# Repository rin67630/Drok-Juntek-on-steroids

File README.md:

# Drok&Juntek on steroids.
Extend the possibilities of cheap digital power supplies with an ESP32 WiFi module

N.B.   The Software part is now on  
https://github.com/rin67630/Soft-Power2-MPPT  
cu there...

Juntek (aka MingHe) and Drok (maybe others e.g Ming-He) sell some interesting cheap programmable buck converter modules e.g.:
- DPS3806         (60V/6A boost/buck converter) https://www.aliexpress.com/item/1005001591485527.html
- Buck3603        (36V/3A buck converter) https://www.aliexpress.com/item/32872687512.html
- BST900          (36V/90V boost converter https://www.aliexpress.com/item/1005002006504263.html
- Drok low Power  (60V/8A buck converter) https://www.aliexpress.com/item/32862110549.html  
- Drok high power (80V/12A buck converter) https://www.aliexpress.com/item/32863179021.html  
*(links only given to identify the modules, you are encouraged to procure the devices from your favourite source)  

They are all controlled by a pluggable control board, which stages a STM microcontroller and a 4x7 digit LED display.  
The 4 push-buttons to control the operations are clumsy and the seven segment display is everything but comfortable.  

My idea was to get rid of the original control module, and to replace it by an ESP32 WiFi enabled microcontroller in order to boost it's usability,
give full internet control and provide tons of features... 

Drok and Juntek are using the same analog control principle:  on the left side, the connector gets two PWM control inputs (voltage and current) and deliver two corresponding analog control feedback outputs all in the range 0..2,1V.  
On the right side, the connector provides GND and 5V at ~200mA.  

I used a TTGO ESP32 with an integrated TFT color display plugged onto a 6x8cm prototyping board as an adapter on a Drok 6008  
showing the web interface on a smartphone:   
  
Here the version with a PCB on a Drok6012 with input and load current probes and a rotary encoder on the extension port:   

The BOM for the upgrade cost less than 20$ (the ESP TTGO, an ADS1115 module, a prototyping board, some pin headers, a few resistors and condensators...)  

## The fun can begin!
Recycling a big part of the software resources of https://github.com/rin67630/Soft-Power-MPPT, I am providing much more than just a simple programmable power supply.

### Power supply mode
The power supply is controllable by:   
- USB -Serial with a simple menu to change the set-points control, the OLED display variants, the charging profiles and print reports.  
- from everywhere in the world using the cloud dashboard service of https://thinger.io with a free limited maker account.  
This is just an example, much more will come:  

- using the integrated buttons of the TTGO and/or an optional rotary knob to make it more comfortable to control.  
- can optionally be remotely controlled by another "slave" TTGO module in the same WiFi area.

Over the serial port and thinger.io, many reports will be made available:  
- Energy report by the second, the minute, the hour.
- Ah, Wh Joule/Coulomb reports by the minutes, the hour, the day.
- Events of the charging process
- ...  

Beside the usual constant voltage and constant current set points, I will provide many interesting things that are not common, but very useful:

### MPPT Solar charger:
cf: https://github.com/rin67630/Soft-Power2-MPPT

### Battery Charger mode: (1)  
- charging profiles for many battery chemistries
- evaluation of the battery's internal resistance
- evaluation of the battery' capacity
- charging time series plots

### Power Source emulation: (1)  
- add a programmable internal resistance
- run a constant power mode
- emulation of solar panel / wind turbine incuding "pseudo-daily" gaussian cycles (accelerated 60x) to test solar chargers

### Programmable Load (for the Juntek buck-boost version) (1)  
- together with a flooder to dissipate the energy, the buck-boost converter can be used to discharge batteries and transfer energy from one battery to another one.  

### Maybe other useful ideas that you might have...

Last but not least everything is neatly self powered, and integrated on one single board, that plugs instead of the original controller board.  
If you wanted to revert to the original functionality, just replug the manufacturer's control board.  
There is absolutely no cable mess and even a new program can be updated over the air using a beginner's easy Arduino IDE.  
You need no additional computer to manage the dashboards, everything is done in the cloud.  
The only thing you need, is a Wifi connection.  

(1) not yet finalized...

You are invited to discuss your personal project on Discord:  
https://discord.gg/gcmSpHH3bX  (Multi purpose Hardware)  
https://discord.gg/eY5H6PMqfk  (Specific application as a MPPT Solar Charge Controller).  

Cu there!

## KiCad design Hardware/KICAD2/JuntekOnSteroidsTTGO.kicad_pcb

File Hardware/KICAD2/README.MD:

New optimized PCB layout Courtesy paulvdh@forum.KiCAD.info.

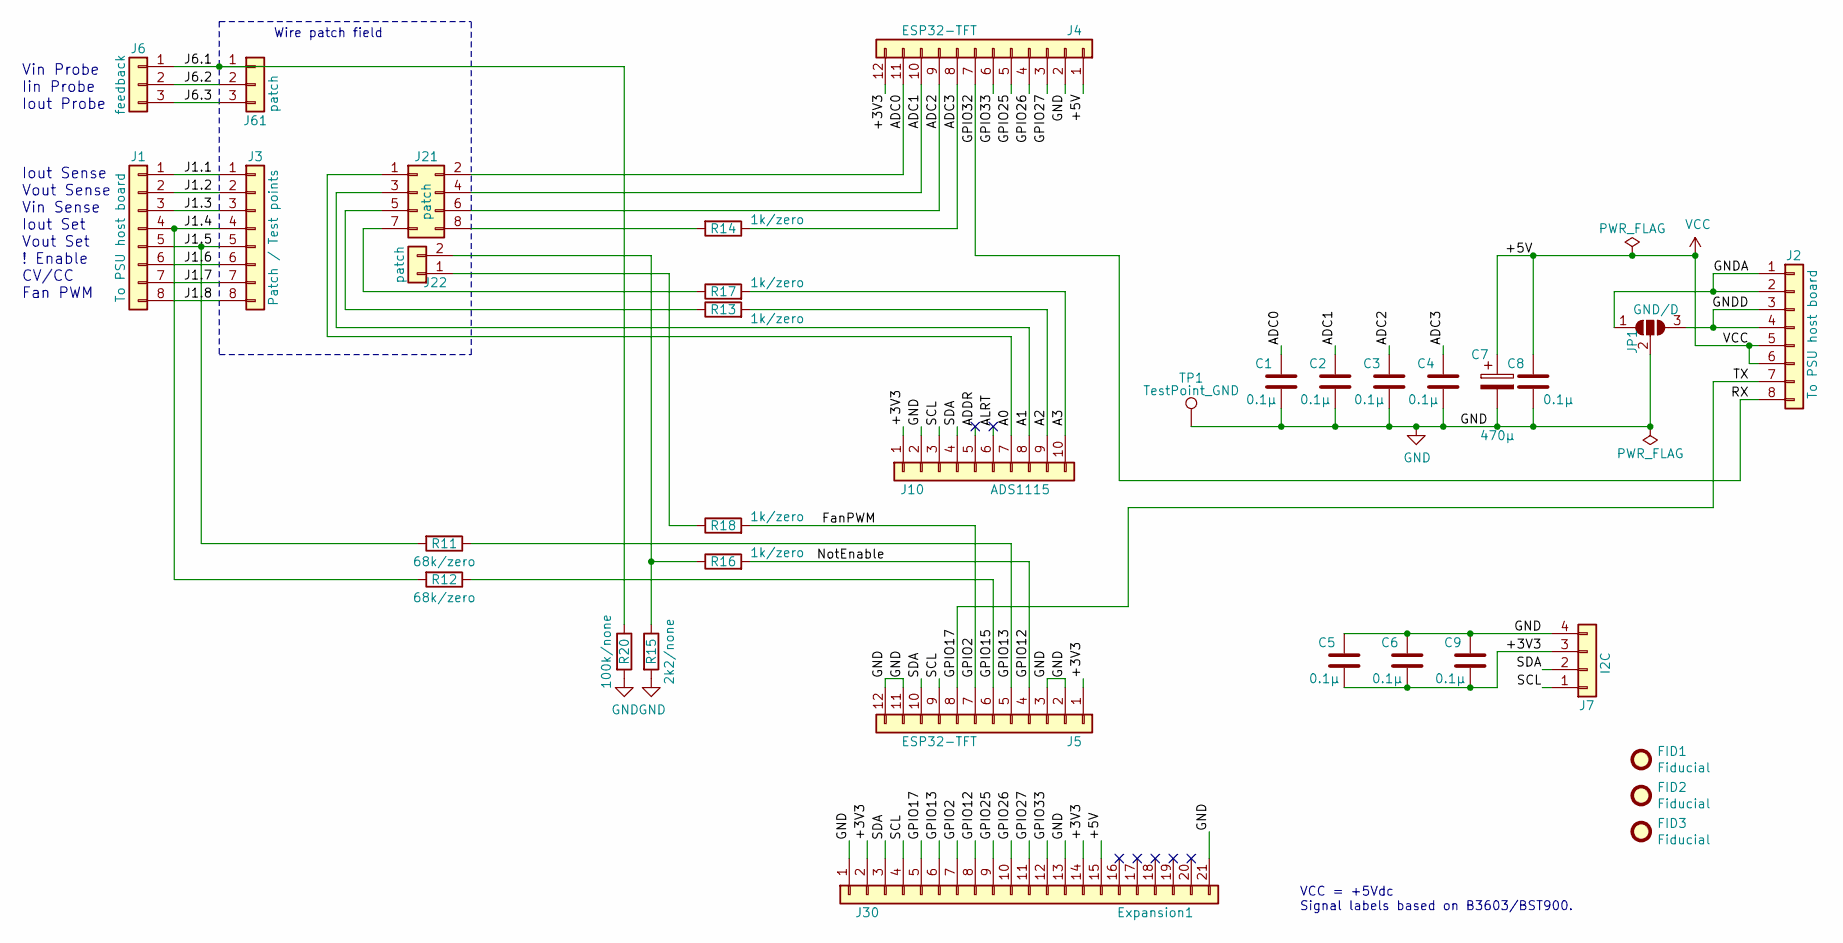
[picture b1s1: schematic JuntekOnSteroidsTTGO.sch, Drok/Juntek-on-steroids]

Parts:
C1, C2, C3, C4, C5, C6, C8, C9: 0.1µ; C_Disc_D3.0mm_W1.6mm_P2.50mm
C7: 470µ; CP_Radial_D8.0mm_P3.50mm
FID1, FID2, FID3: Fiducial; Fiducial_0.5mm_Mask1mm
J1, J2: To PSU host board; PinHeader_1x08_P2.54mm_Vertical
J3: Patch / Test points; PinHeader_1x08_P2.54mm_Vertical
J4, J5: ESP32-TFT; PinSocket_1x12_P2.54mm_Vertical
J6: feedback; PinHeader_1x03_P2.54mm_Horizontal
J7: I2C; JST_PH_B4B-PH-K_1x04_P2.00mm_Vertical
J10: ADS1115; PinSocket_1x10_P2.54mm_Vertical
J21: patch; PinHeader_2x04_P2.54mm_Vertical
J22: patch; PinHeader_1x02_P2.54mm_Vertical
J30: Expansion1; PinHeader_1x21_P2.54mm_Horizontal
J61: patch; PinHeader_1x03_P2.54mm_Vertical
JP1: GND/D; SolderJumper-3_P1.3mm_Open_RoundedPad1.0x1.5mm
R11, R12: 68k/zero; R_Axial_DIN0204_L3.6mm_D1.6mm_P7.62mm_Horizontal
R13, R14, R16, R17, R18: 1k/zero; R_Axial_DIN0204_L3.6mm_D1.6mm_P7.62mm_Horizontal
R15: 2k2/none; R_Axial_DIN0204_L3.6mm_D1.6mm_P7.62mm_Horizontal
R20: 100k/none; R_Axial_DIN0204_L3.6mm_D1.6mm_P7.62mm_Horizontal
TP1: TestPoint_GND; Pin_D1.3mm_L11.0mm

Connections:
/+3V3: C5.2, C6.2, C9.2, J4.12, J5.1, J7.3, J10.1, J30.2, J30.14
/A0: J10.7, J21.1
/A1: J10.8, J21.3
/A2: J10.9, R13.2
/A3: J10.10, R17.2
/ADC0: C1.1, J4.11, J21.2
/ADC1: C2.1, J4.10, J21.4
/ADC2: C3.1, J4.9, J21.6
/ADC3: C4.1, J4.8, R14.1
/FanPWM: J5.7, J30.7, R18.2
/GNDA: J2.1, J2.2, JP1.1 (A)
/GNDD: J2.3, J2.4, JP1.3 (B)
/GPIO12: J5.4, J30.8, R16.2
/GPIO13: J5.5, J30.6, R11.1
/GPIO15: J5.6, R12.1
/GPIO17: J2.7, J5.8, J30.5
/GPIO25: J4.5, J30.9
/GPIO26: J4.4, J30.10
/GPIO27: J4.3, J30.11
/GPIO32: J2.8, J4.7
/GPIO33: J4.6, J30.12
/J1.1: J1.1, J3.1
/J1.2: J1.2, J3.2
/J1.3: J1.3, J3.3
/J1.4: J1.4, J3.4, R12.2
/J1.5: J1.5, J3.5, R11.2
/J1.6: J1.6, J3.6
/J1.7: J1.7, J3.7
/J1.8: J1.8, J3.8
/J6.1: J6.1, J61.1, R20.1
/J6.2: J6.2, J61.2
/J6.3: J6.3, J61.3
/SCL: J5.9, J7.1, J10.3, J30.4
/SDA: J5.10, J7.2, J10.4, J30.3
GND: C1.2, C2.2, C3.2, C4.2, C5.1, C6.1, C7.2, C8.2, C9.1, J4.2, J5.2, J5.3, J5.11, J5.12, J7.4, J10.2, J30.1, J30.13, J30.21, JP1.2 (C), R15.2, R20.2, TP1.1
unnamed: J21.5, R13.1
unnamed: J21.7, R17.1
unnamed: J21.8, R14.2
unnamed: J22.1, R18.1
unnamed: J22.2, R15.1, R16.1
VCC: C7.1, C8.1, J2.5, J2.6, J4.1, J30.15

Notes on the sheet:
VCC = +5Vdc Signal labels based on B3603/BST900.
Wire patch field
Vin Probe Iin Probe Iout Probe
Iout Sense Vout Sense Vin Sense Iout Set Vout Set ! Enable CV/CC Fan PWM

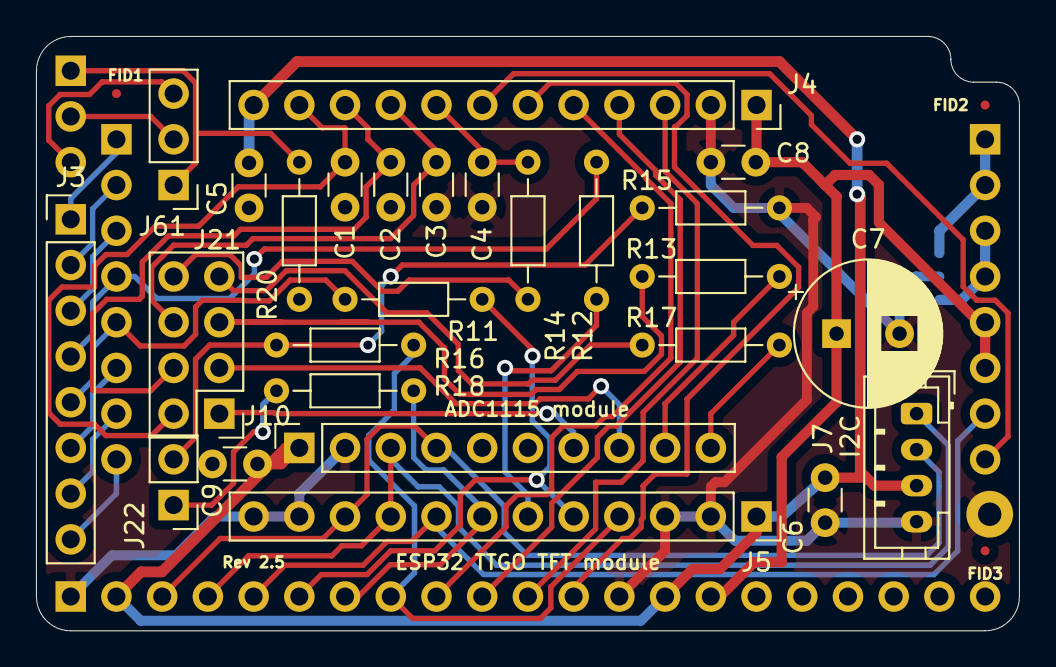
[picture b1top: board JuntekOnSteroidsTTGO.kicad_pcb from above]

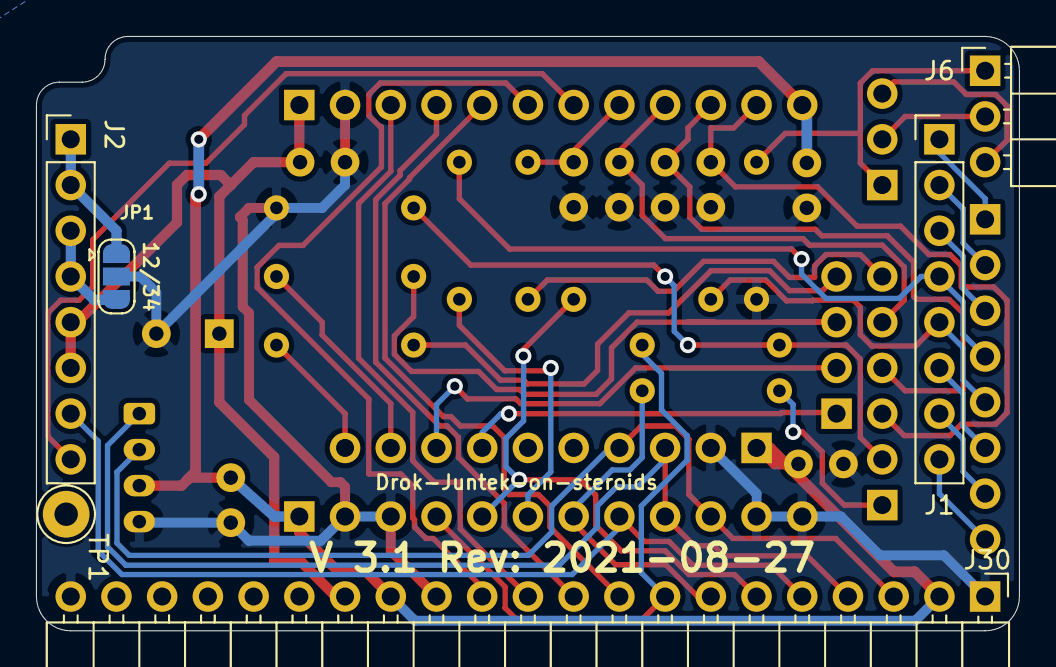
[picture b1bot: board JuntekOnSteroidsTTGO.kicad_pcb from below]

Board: 2 copper layers, 54.6 x 33.0 mm, 35 parts (6 on the bottom side), 41 nets.

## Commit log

2021-03-09 Create a0_Parameters
2021-03-09 Create a1_Libs___Vars
2021-03-09 Create b_Functions
2021-03-09 Create c_Setup
2021-03-09 Create d_Menu
2021-03-09 Create e_Data
2021-03-09 Create f_Display
2021-03-09 Create g_Serial
2021-03-09 Create h_Wireless
2021-03-09 Rename a0_Parameters to a0_Parameters.ino
2021-03-09 Rename a1_Libs___Vars to a1_Libs___Vars.ino
2021-03-09 Rename b_Functions to b_Functions.ino
2021-03-09 Rename c_Setup to c_Setup.ino
2021-03-09 Rename d_Menu to d_Menu.ino
2021-03-09 Rename e_Data to e_Data.ino
2021-03-09 Rename f_Display to f_Display.ino
2021-03-09 Rename g_Serial to g_Serial.ino
2021-03-09 Rename h_Wireless to h_Wireless.ino
2021-03-09 Rename ReadMe.md to 0.ReadMe.md
2021-03-15 Preconfigured Dashboard
    Preconfigured Thinger Dashboard, replace all occurences of "User" by your user name and all occurences of "JuntekNT" by your device name.
2021-03-15 Rename Thinger_Dashboard.ino to Thinger_Dashboard.json
2021-03-15 Customized User_Setup.h
    Customized User_Setup.h should replace [Arduino User Folder]/libraries/TFT_eSPI/User_Setup.h
2021-04-15 Rename Menu_system.md to 2_Menu_system.md
2021-04-15 Rename Thinger_Dashboard.json to Dashboard_json.h
2021-04-15 Rename Starting_at_Thinger.io.md to 3_Starting_at_Thinger.io.md
2021-04-15 Create 4_Configuration instructions
2021-04-15 Rename 4_Configuration instructions to 4_Configuration_instructions
2021-04-15 Rename 4_Configuration_instructions to 4_Configuration_instructions.md
2021-04-15 Create Juntek3806h
2021-07-07 Rename Connectors description.mdMD to Connectors description.md
2021-08-07 Rename J3603.h to SoftPower_HAL_Files.J3603.h
2021-08-07 Rename Software/SoftPower_HAL_Files.J3603.h to Software/SoftPower_HAL_Files/J3603.h
2021-08-07 Create SoftPower_HAL_Files
2021-08-07 Rename Software/J3603.h to Software/libraries/SoftPower_HAL_Files/J3603.h
2021-08-26 Create README.MD
    Here are all files needed by KiCAD to generate a PCB.
2021-08-26 Create README.MD
    Here are the Fab files to manufacture the PCB
2021-08-27 Create README.MD
    Here the PCB production files...
2022-04-18 Add files via upload
    Corrected the patch assignments to PCB
2023-03-05 Rename Folder to match project name
2024-03-07 Add files via upload
    For a TTGO: Replace the User_Setup.h file in /libaries/TFT_eSPI/
2024-03-08 Create Caveat if you use a TTGO-Display.md
    Please read before compiling for the TTGO-T1 !
2024-04-20 Update README.md
    Links to hardware updated
